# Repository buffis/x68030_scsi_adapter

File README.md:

# x68030_scsi_adapter

X68030 Internal SCSI adapter.

See https://buffis.com/old-hardware/retro-computers/the-x68030-scsi-adventure-part-2/

## BOM

- C1-C18: C0805X470J1HACTU (or any other 47pF 0805 cap)
- RN1, RN2: 4611X-104-221/331L
- F1: MFU0805FF01000P500 (or other 1A 0805 fuse)
- J1: 10129381-950002BLF (2.54mm pitch pin header)
- J2: 57102-G06-20LF (2.00mm pitch pin header)
- J3: B2B-XH-2-TV4 (JST XH 2 pin)... or just use a 2.54mm pin header.
- U1: SN74LVC1G14DBVTE4 or similar. Needs to be able to sink >10mA.

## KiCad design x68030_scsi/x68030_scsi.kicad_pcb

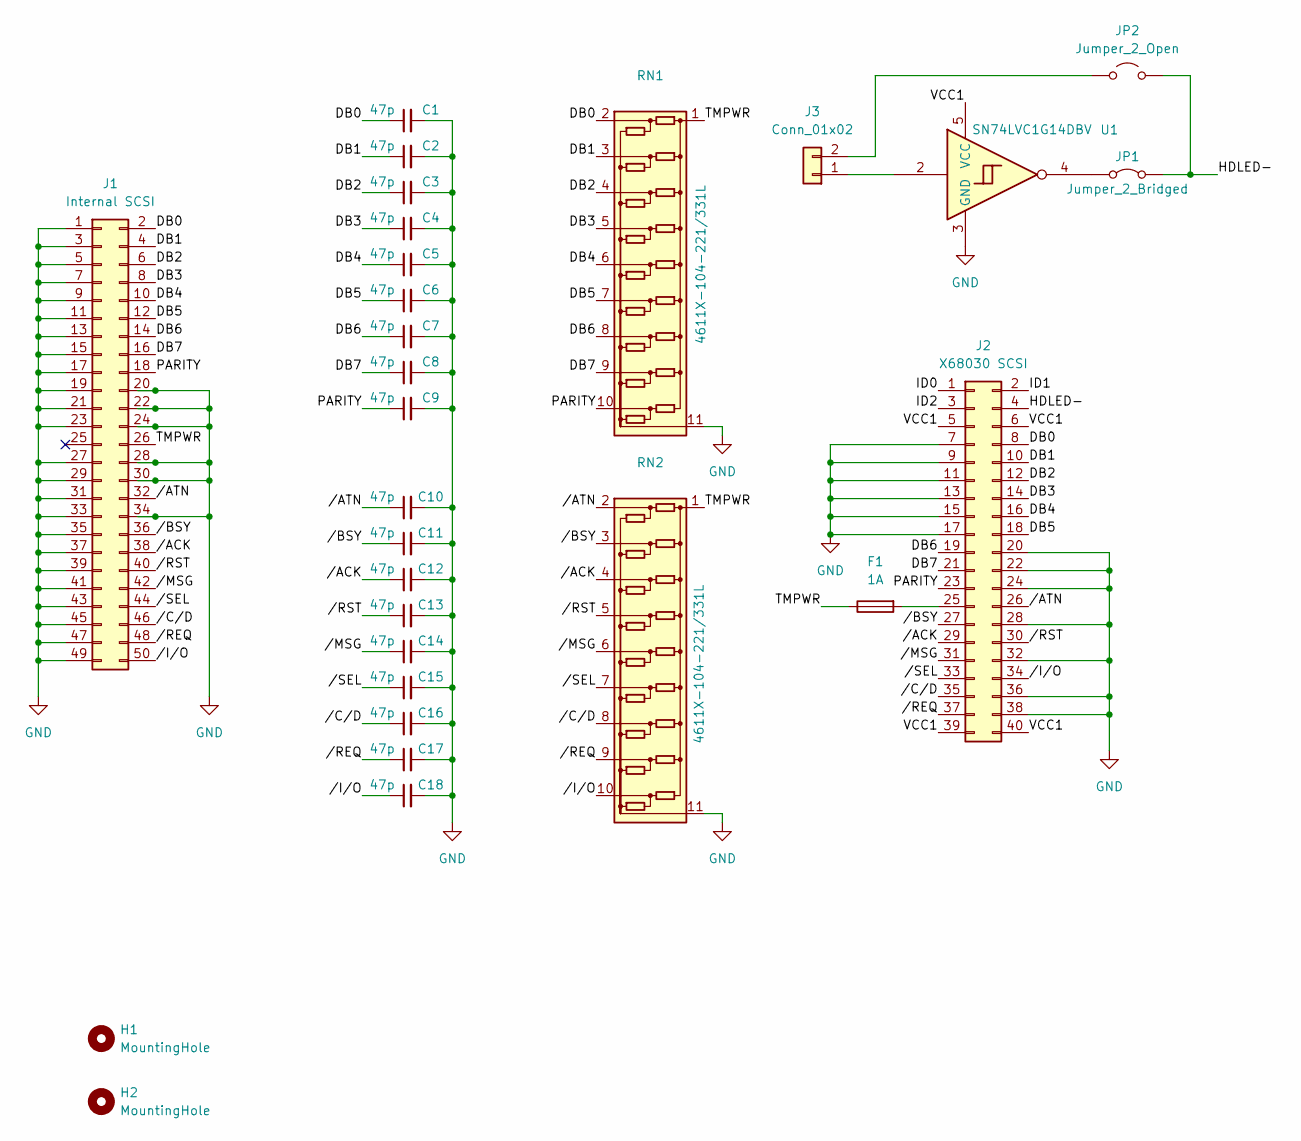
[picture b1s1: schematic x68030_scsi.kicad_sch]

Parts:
C1, C2, C3, C4, C5, C6, C7, C8, C9, C10, C11, C12, C13, C14, C15, C16, C17, C18: 47p; C_0805_2012Metric_Pad1.18x1.45mm_HandSolder; Mouser 80-C0805X470J1HACTU
F1: 1A; Fuse_0805_2012Metric_Pad1.15x1.40mm_HandSolder; Mouser 594-MFU0805-FF-1.0
H1, H2: MountingHole; MountingHole_4.3mm_M4
J1: Internal SCSI; IDC-Header_2x25_P2.54mm_Vertical; Mouser 737-BHR-50-VUA
J2: X68030 SCSI; PinHeader_2x20_P2.00mm_Vertical; Mouser 538-87831-4021
J3: Conn_01x02; JST_XH_B2B-XH-A_1x02_P2.50mm_Vertical
JP1: Jumper_2_Bridged; SolderJumper-2_P1.3mm_Bridged_Pad1.0x1.5mm
JP2: Jumper_2_Open; SolderJumper-2_P1.3mm_Open_Pad1.0x1.5mm
RN1, RN2: 4611X-104-221/331L; R_Array_SIP11; Mouser 652-4611X104221/331L
U1: SN74LVC1G14DBV; SOT-23-5; Mouser 595-74LVC1G14DBVTE4

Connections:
/DB0: C1.1, J1.2, J2.8, RN1.2 (R1)
/DB1: C2.1, J1.4, J2.10, RN1.3 (R2)
/DB2: C3.1, J1.6, J2.12, RN1.4 (R3)
/DB3: C4.1, J1.8, J2.14, RN1.5 (R4)
/DB4: C5.1, J1.10, J2.16, RN1.6 (R5)
/DB5: C6.1, J1.12, J2.18, RN1.7 (R6)
/DB6: C7.1, J1.14, J2.19, RN1.8 (R7)
/DB7: C8.1, J1.16, J2.21, RN1.9 (R8)
/HDLED-: J2.4, JP1.2 (B), JP2.2 (B)
/ID0: J2.1
/ID1: J2.2
/ID2: J2.3
/PARITY: C9.1, J1.18, J2.23, RN1.10 (R9)
/TMPWR: F1.1, J1.26, RN1.1 (COM1), RN2.1 (COM1)
/VCC1: J2.5, J2.6, J2.39, J2.40, U1.5 (VCC)
//ACK: C12.1, J1.38, J2.29, RN2.4 (R3)
//ATN: C10.1, J1.32, J2.26, RN2.2 (R1)
//BSY: C11.1, J1.36, J2.27, RN2.3 (R2)
//C/D: C16.1, J1.46, J2.35, RN2.8 (R7)
//I/O: C18.1, J1.50, J2.34, RN2.10 (R9)
//MSG: C14.1, J1.42, J2.31, RN2.6 (R5)
//REQ: C17.1, J1.48, J2.37, RN2.9 (R8)
//RST: C13.1, J1.40, J2.30, RN2.5 (R4)
//SEL: C15.1, J1.44, J2.33, RN2.7 (R6)
GND: C1.2, C2.2, C3.2, C4.2, C5.2, C6.2, C7.2, C8.2, C9.2, C10.2, C11.2, C12.2, C13.2, C14.2, C15.2, C16.2, C17.2, C18.2, J1.1, J1.3, J1.5, J1.7, J1.9, J1.11, J1.13, J1.15, J1.17, J1.19, J1.20, J1.21, J1.22, J1.23, J1.24, J1.27, J1.28, J1.29, J1.30, J1.31, J1.33, J1.34, J1.35, J1.37, J1.39, J1.41, J1.43, J1.45, J1.47, J1.49, J2.7, J2.9, J2.11, J2.13, J2.15, J2.17, J2.20, J2.22, J2.24, J2.28, J2.32, J2.36, J2.38, RN1.11 (COM2), RN2.11 (COM2), U1.3 (GND)
unnamed: F1.2, J2.25
unnamed: J3.1, U1.2
unnamed: J3.2, JP2.1 (A)
unnamed: JP1.1 (A), U1.4

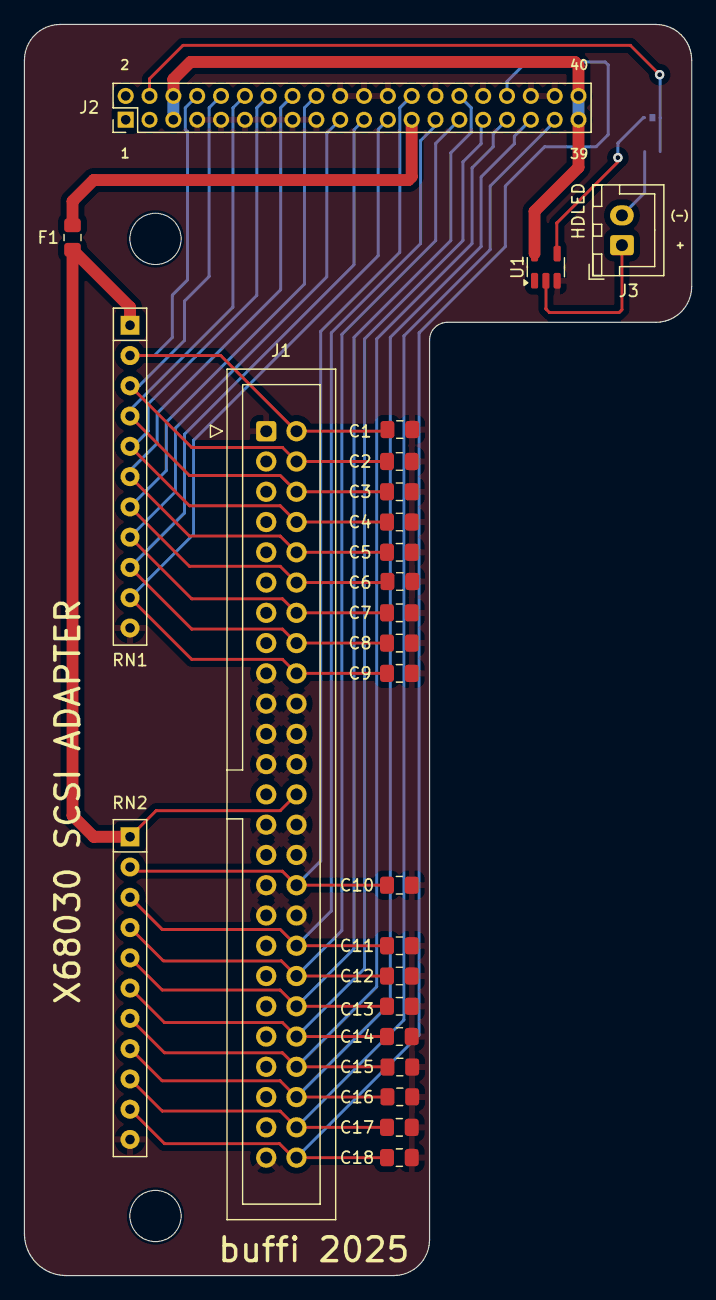
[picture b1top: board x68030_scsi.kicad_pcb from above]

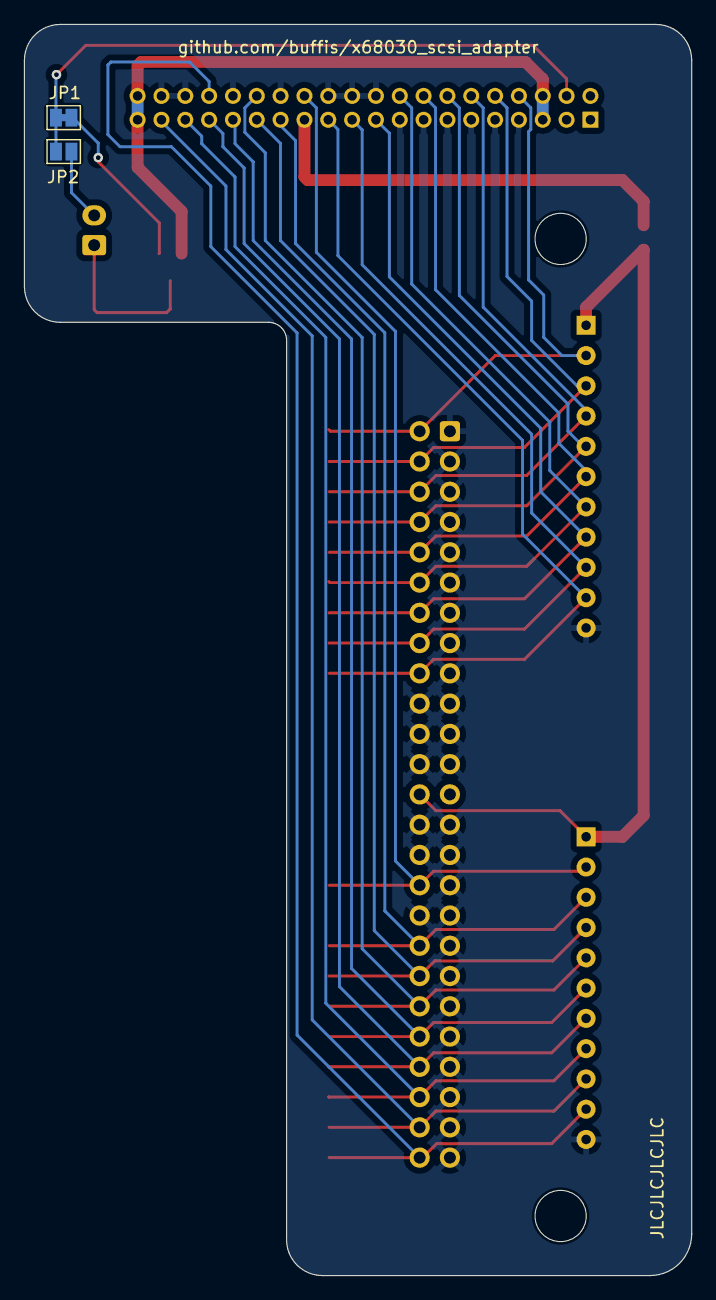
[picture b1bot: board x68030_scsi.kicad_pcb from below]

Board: 2 copper layers, 56.0 x 105.0 mm, 29 parts (2 on the bottom side), 26 nets.

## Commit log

2025-01-30 initial version
2025-01-30 misc
2025-02-01 fixes
2025-02-03 new gerbers
2025-02-17 minor fixes
2025-02-19 fix stuff
2025-02-19 gerbers
2025-02-28 back covers
